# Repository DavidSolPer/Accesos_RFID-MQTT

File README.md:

# Accesos_RFID-MQTT
PROYECTO DE GESTIÓN DE ACCESOS A EDIFICIOS MEDIANTE RFID y MQTT.
El Hardware base utilizado para el proyecto es la placa de desarrollo NodeMCU, ésta placa incluye el ESP8266 por lo que es
posible conectarse vía Wifi a un servidor. Se trata de una tarjeta muy versátil, ya que cuenta con GPIOS con distintas
funcionalidades, es posible utilizarlos como entradas y salidas, se puede generar una señal PWM, cuenta con un ADC, soporta
UART, ISP, I²C, etc... Además de ser muy asequible, con un precio de menos de 8 dólares. El sensor RFID utilizado será el 
RC-522.
El NodeMCU se puede programar el Lua, cargando un Firmware a la memoria Flash que hará las veces de intérprete. También es
posible programarlo en una implementación de Python llamada Micropython y en lenguaje Arduino. Cuando se usa un intérprete de
Lua se puede cargar un Firmware completo o se puede generar un Firmware "Custom" (https://nodemcu-build.com/) con las
funcionalidades o recursos que se deseen habilitar para usar en el proyecto, para cargarlo con alguna herramienta como
ESPtool Master (https://github.com/themadinventor/esptool), ésto es muy útil ya que permite optimizar la poca memoria que
posee el NodeMCU. En mi caso yo utilicé lenguaje Arduino para la programación, ya que no es necesario cargar un Firmware
previamente, la compilación genera un fichero .bin que se graba desde la posición 0x00 de Flash. 
En cada uno de los accesos o puertas se montará un punto de acceso que consiste en el NodeMCU, el módulo RFID, un led RGB
para visualizar el estado (Azul= Esperando TAG, Verde=Aceptado, Rojo= Rechazado), una etapa de potencia para accionar el
Solenoide de una chapa electromagnética, y la fuente de alimentación para todo el circuito. La etapa de potencia cambia de
estado dependiendo de la señal que llega al pin del led verde del RGB.
Para la gestión de los accesos se utiliza MQTT, un protocolo de Iot utilizado para la comunicación entre dispositivos
mediante mensajes cortos de la forma:
Tópico/Mensaje
Los mensajes son gestionados por algún servidor o también llamado Broker de MQTT, el que yo utilizo es Mosquitto
(https://mosquitto.org/), en éste se debe de subscribir a un tópico general de los puntos de acceso para recibir sólo éstos 
mensajes, comprobar los UID que envía el NodeMCU en una base de datos y regresar un mensaje para que el NodeMCU evalúe si
se permitirá el acceso del usario o no. 

NOTAS IMPORTANTES:
> Dependiendo del modelo de NodeMCU necesitarás pulsar el botón FLASH de la placa cada vez que requieras cargar el programas.
O si quieres montar el proyecto en un módulo ESP, es necesario utilizar un convertidor USB-Serial con una ALIMENTACIÓN DE 3.3
Vcc y relizar un puente entre GPIO0 y GND para programar el módulo.
> Es necesario contar con una versión del IDE de Arduino 1.6.11 o superior y agregar soporte para los módulos ESP.

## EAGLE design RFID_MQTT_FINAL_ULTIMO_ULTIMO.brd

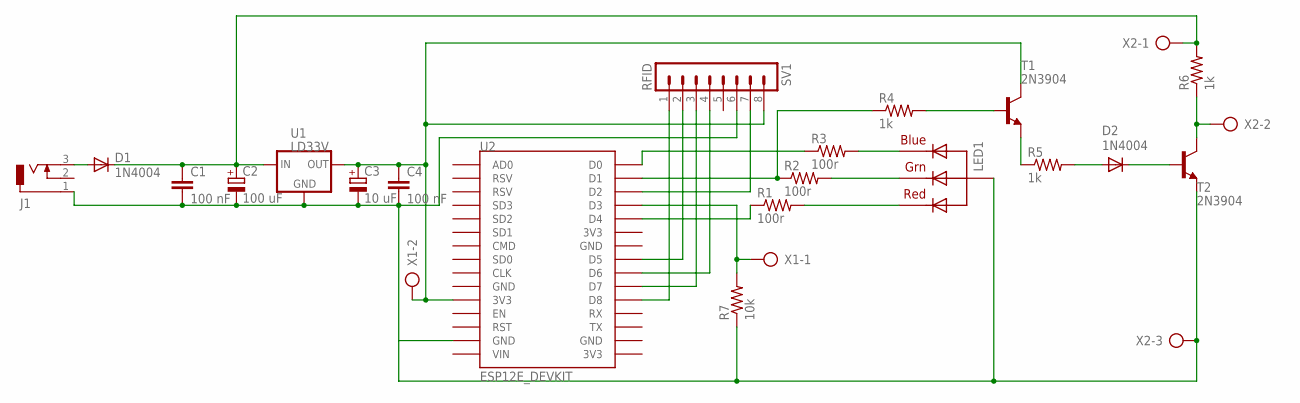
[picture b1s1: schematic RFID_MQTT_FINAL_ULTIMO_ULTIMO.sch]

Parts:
C1, C4: 100 nF; C050-024X044
C2: 100 uF; E3,5-8
C3: 10 uF; E3,5-8
D1, D2: 1N4004; DO41-10
J1: DCJ0202
LED1: RGBLED_CA-5MM; LED5MMRGB
R1, R2, R3: 100r; 0207/7
R4, R5, R6: 1k; 0207/7
R7: 10k; 0207/7
SV1: RFID; MA08-1
T1, T2: 2N3904; TO92
U1: LD33V; LD1117V33
U2: ESP12E_DEVKIT
X1: AK500/2-H
X2: AK500/3-H

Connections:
unnamed: D1.A, J1.3
unnamed 2: C1.1, C2.+, D1.C, R6.2, U1.IN, X2.1; also elsewhere on the board
unnamed: R4.2, T1.2 (B)
unnamed 4: C3.+, C4.1, SV1.8, T1.1 (C), U1.OUT, U2.3V3@0 (3V3), X1.2; also elsewhere on the board
unnamed 5: SV1.7, U2.D2; also elsewhere on the board
unnamed 6: SV1.1, U2.D8; also elsewhere on the board
unnamed 7: SV1.2, U2.D5; also elsewhere on the board
unnamed 8: SV1.3, U2.D7; also elsewhere on the board
unnamed 9: SV1.4, U2.D6; also elsewhere on the board
unnamed: LED1.4 (BLUE), R3.2
unnamed 11: C1.2, C2.-, C3.-, C4.2, J1.1, LED1.2 (VCC), R7.1, SV1.6, T2.3 (E), U1.GND, U2.GND@1 (GND), X2.3; also elsewhere on the board
unnamed: LED1.1 (RED), R1.2
unnamed 13: R3.1, U2.D0; also elsewhere on the board
unnamed 14: R2.1, R4.1, U2.D1; also elsewhere on the board
unnamed 15: R1.1, U2.D4; also elsewhere on the board
unnamed: R5.1, T1.3 (E)
unnamed: D2.A, R5.2
unnamed: D2.C, T2.2 (B)
unnamed: R6.1, T2.1 (C), X2.2
unnamed: LED1.3 (GREEN), R2.2
unnamed 21: R7.2, U2.D3, X1.1; also elsewhere on the board

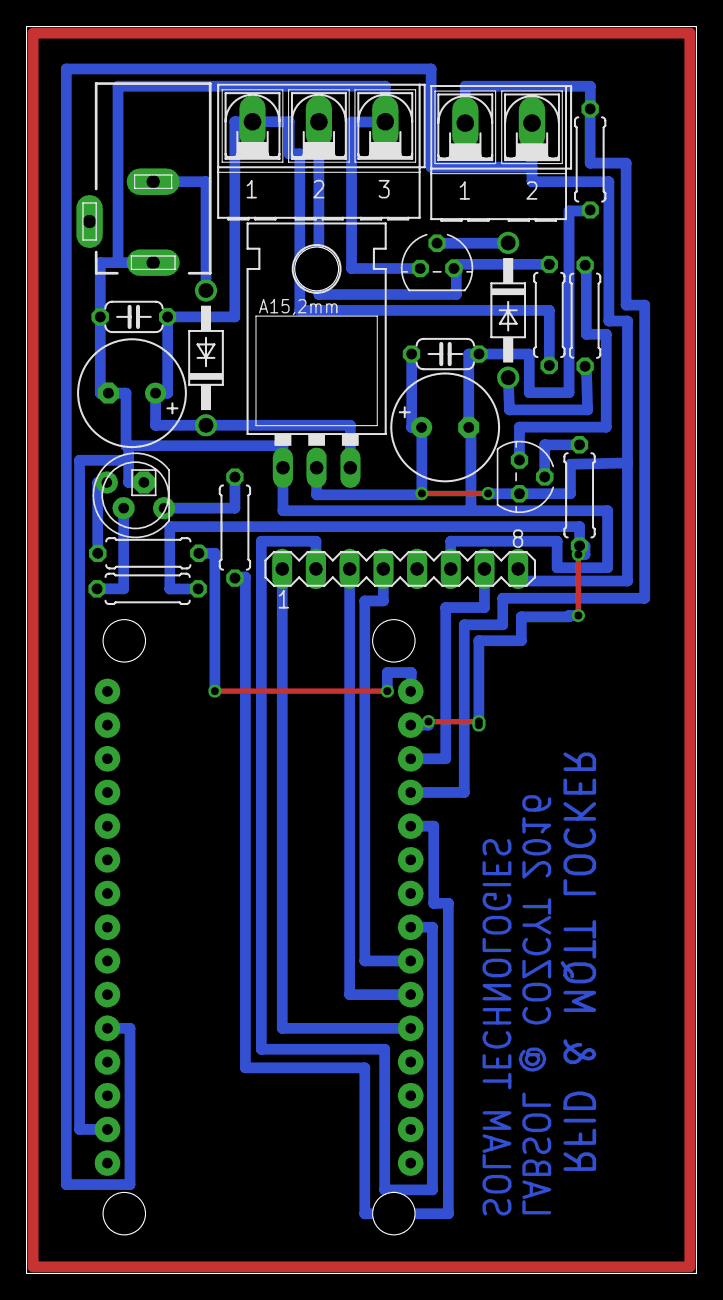
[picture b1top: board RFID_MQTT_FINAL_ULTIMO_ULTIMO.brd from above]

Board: 2 copper layers, 50.5 x 94.0 mm, 22 parts (0 on the bottom side), 21 nets.

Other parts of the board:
U$1: LD33V; LD1117V33
U$2: ESP12E_DEVKIT

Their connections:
unnamed 2: U$1.IN; also elsewhere on the board
unnamed 4: U$1.OUT, U$2.3V3@0; also elsewhere on the board
unnamed 5: U$2.D2; also elsewhere on the board
unnamed 6: U$2.D8; also elsewhere on the board
unnamed 7: U$2.D5; also elsewhere on the board
unnamed 8: U$2.D7; also elsewhere on the board
unnamed 9: U$2.D6; also elsewhere on the board
unnamed 11: U$1.GND, U$2.GND@1; also elsewhere on the board
unnamed 13: U$2.D0; also elsewhere on the board
unnamed 14: U$2.D1; also elsewhere on the board
unnamed 15: U$2.D4; also elsewhere on the board
unnamed 21: U$2.D3; also elsewhere on the board

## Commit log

2016-11-30 PCB Eagle's Design File
2016-11-30 SCHEMATIC EAGLE's DESIGN FILE
